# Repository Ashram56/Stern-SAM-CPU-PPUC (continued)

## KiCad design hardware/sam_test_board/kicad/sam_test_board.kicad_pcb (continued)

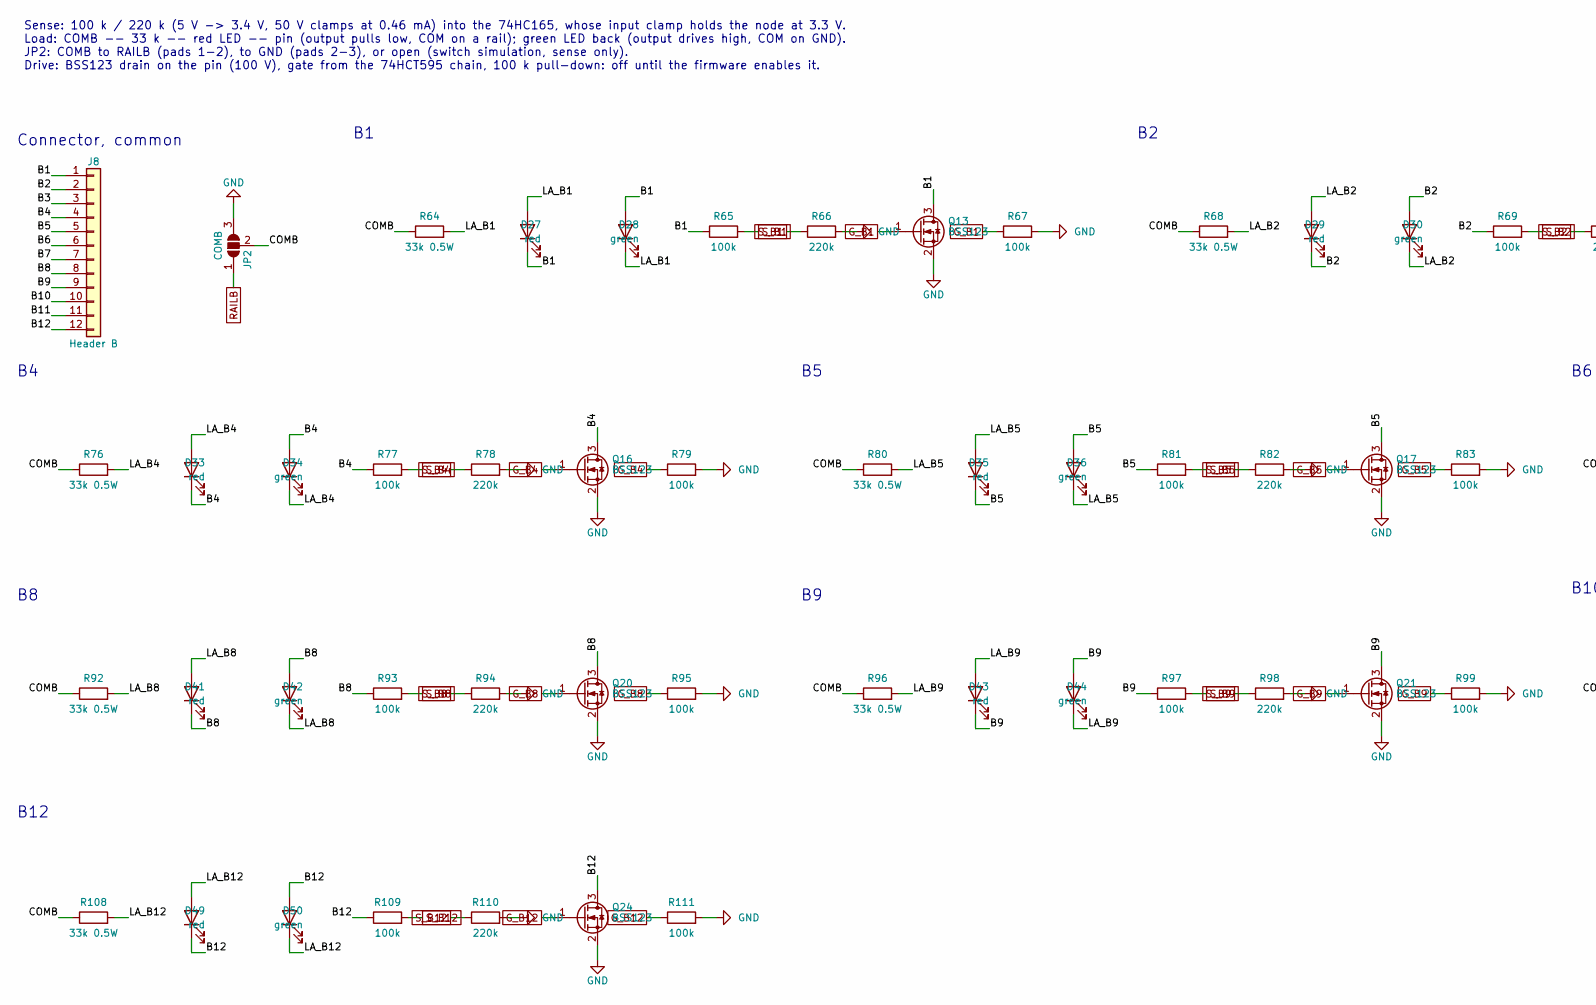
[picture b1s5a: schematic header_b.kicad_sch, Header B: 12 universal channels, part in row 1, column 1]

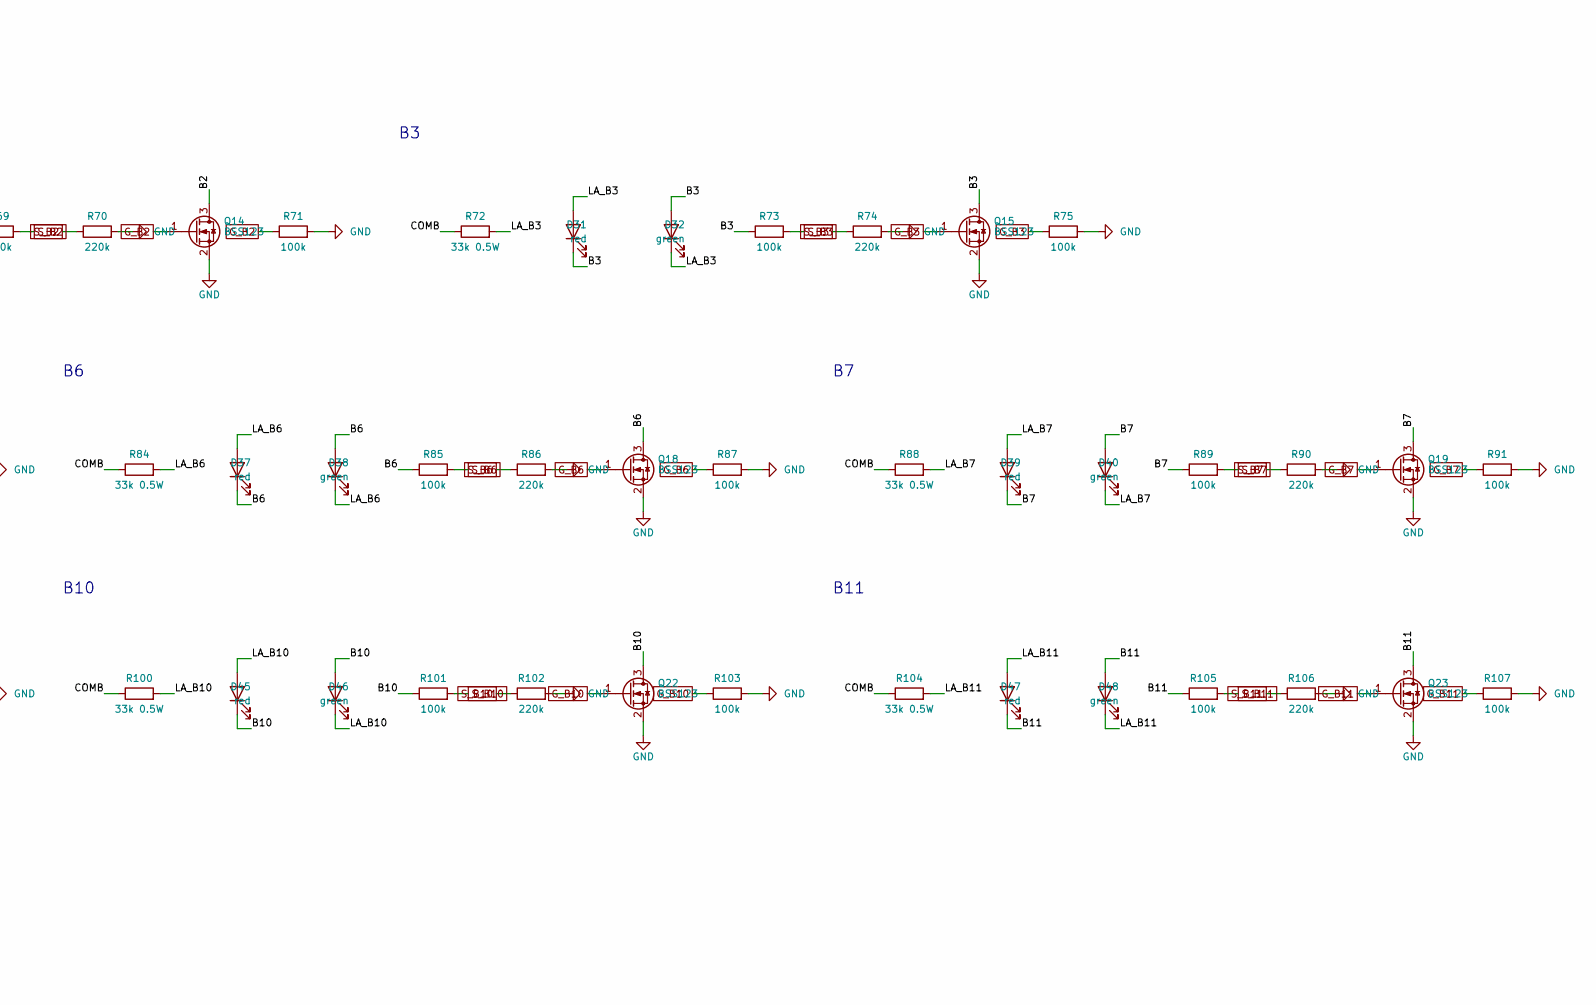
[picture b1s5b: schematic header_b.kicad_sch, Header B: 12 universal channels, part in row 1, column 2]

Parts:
D27, D29, D31, D33, D35, D37, D39, D41, D43, D45, D47, D49: red; LED_0805_2012Metric
D28, D30, D32, D34, D36, D38, D40, D42, D44, D46, D48, D50: green; LED_0805_2012Metric
J8: Header B; Molex_KK-396_A-41791-0012_1x12_P3.96mm_Vertical
JP2: COMB; SolderJumper-3_P1.3mm_Open_Pad1.0x1.5mm
Q13, Q14, Q15, Q16, Q17, Q18, Q19, Q20, Q21, Q22, Q23, Q24: BSS123; SOT-23
R64, R68, R72, R76, R80, R84, R88, R92, R96, R100, R104, R108: 33k 0.5W; R_0805_2012Metric
R65, R67, R69, R71, R73, R75, R77, R79, R81, R83, R85, R87, R89, R91, R93, R95, R97, R99, R101, R103, R105, R107, R109, R111: 100k; R_0805_2012Metric
R66, R70, R74, R78, R82, R86, R90, R94, R98, R102, R106, R110: 220k; R_0805_2012Metric

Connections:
/Header B/B1: D27.1 (K), D28.2 (A), J8.1, Q13.3 (D), R65.1
/Header B/B2: D29.1 (K), D30.2 (A), J8.2, Q14.3 (D), R69.1
/Header B/B3: D31.1 (K), D32.2 (A), J8.3, Q15.3 (D), R73.1
/Header B/B4: D33.1 (K), D34.2 (A), J8.4, Q16.3 (D), R77.1
/Header B/B5: D35.1 (K), D36.2 (A), J8.5, Q17.3 (D), R81.1
/Header B/B6: D37.1 (K), D38.2 (A), J8.6, Q18.3 (D), R85.1
/Header B/B7: D39.1 (K), D40.2 (A), J8.7, Q19.3 (D), R89.1
/Header B/B8: D41.1 (K), D42.2 (A), J8.8, Q20.3 (D), R93.1
/Header B/B9: D43.1 (K), D44.2 (A), J8.9, Q21.3 (D), R97.1
/Header B/B10: D45.1 (K), D46.2 (A), J8.10, Q22.3 (D), R101.1
/Header B/B11: D47.1 (K), D48.2 (A), J8.11, Q23.3 (D), R105.1
/Header B/B12: D49.1 (K), D50.2 (A), J8.12, Q24.3 (D), R109.1
/Header B/COMB: JP2.2 (C), R64.1, R68.1, R72.1, R76.1, R80.1, R84.1, R88.1, R92.1, R96.1, R100.1, R104.1, R108.1
/Header B/LA_B1: D27.2 (A), D28.1 (K), R64.2
/Header B/LA_B2: D29.2 (A), D30.1 (K), R68.2
/Header B/LA_B3: D31.2 (A), D32.1 (K), R72.2
/Header B/LA_B4: D33.2 (A), D34.1 (K), R76.2
/Header B/LA_B5: D35.2 (A), D36.1 (K), R80.2
/Header B/LA_B6: D37.2 (A), D38.1 (K), R84.2
/Header B/LA_B7: D39.2 (A), D40.1 (K), R88.2
/Header B/LA_B8: D41.2 (A), D42.1 (K), R92.2
/Header B/LA_B9: D43.2 (A), D44.1 (K), R96.2
/Header B/LA_B10: D45.2 (A), D46.1 (K), R100.2
/Header B/LA_B11: D47.2 (A), D48.1 (K), R104.2
/Header B/LA_B12: D49.2 (A), D50.1 (K), R108.2
GND: JP2.3 (B), Q13.2 (S), Q14.2 (S), Q15.2 (S), Q16.2 (S), Q17.2 (S), Q18.2 (S), Q19.2 (S), Q20.2 (S), Q21.2 (S), Q22.2 (S), Q23.2 (S), Q24.2 (S), R66.2, R67.2, R70.2, R71.2, R74.2, R75.2, R78.2, R79.2, R82.2, R83.2, R86.2, R87.2, R90.2, R91.2, R94.2, R95.2, R98.2, R99.2, R102.2, R103.2, R106.2, R107.2, R110.2, R111.2; also elsewhere on the board
G_B1: Q13.1 (G), R67.1; also elsewhere on the board
G_B2: Q14.1 (G), R71.1; also elsewhere on the board
G_B3: Q15.1 (G), R75.1; also elsewhere on the board
G_B4: Q16.1 (G), R79.1; also elsewhere on the board
G_B5: Q17.1 (G), R83.1; also elsewhere on the board
G_B6: Q18.1 (G), R87.1; also elsewhere on the board
G_B7: Q19.1 (G), R91.1; also elsewhere on the board
G_B8: Q20.1 (G), R95.1; also elsewhere on the board
G_B9: Q21.1 (G), R99.1; also elsewhere on the board
G_B10: Q22.1 (G), R103.1; also elsewhere on the board
G_B11: Q23.1 (G), R107.1; also elsewhere on the board
G_B12: Q24.1 (G), R111.1; also elsewhere on the board
RAILB: JP2.1 (A); also elsewhere on the board
S_B1: R65.2, R66.1; also elsewhere on the board
S_B2: R69.2, R70.1; also elsewhere on the board
S_B3: R73.2, R74.1; also elsewhere on the board
S_B4: R77.2, R78.1; also elsewhere on the board
S_B5: R81.2, R82.1; also elsewhere on the board
S_B6: R85.2, R86.1; also elsewhere on the board
S_B7: R89.2, R90.1; also elsewhere on the board
S_B8: R93.2, R94.1; also elsewhere on the board
S_B9: R97.2, R98.1; also elsewhere on the board
S_B10: R101.2, R102.1; also elsewhere on the board
S_B11: R105.2, R106.1; also elsewhere on the board
S_B12: R109.2, R110.1; also elsewhere on the board

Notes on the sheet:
Sense: 100 k / 220 k (5 V -> 3.4 V, 50 V clamps at 0.46 mA) into the 74HC165, whose input clamp holds the node at 3.3 V. Load: COMB -- 33 k -- red LED -- pin (output pulls low, COM on a rail); green LED back (output drives high, COM on GND). JP2: COMB to RAILB (pads 1-2), to GND (pads 2-3), or open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
Connector, common
B10
B11
B12

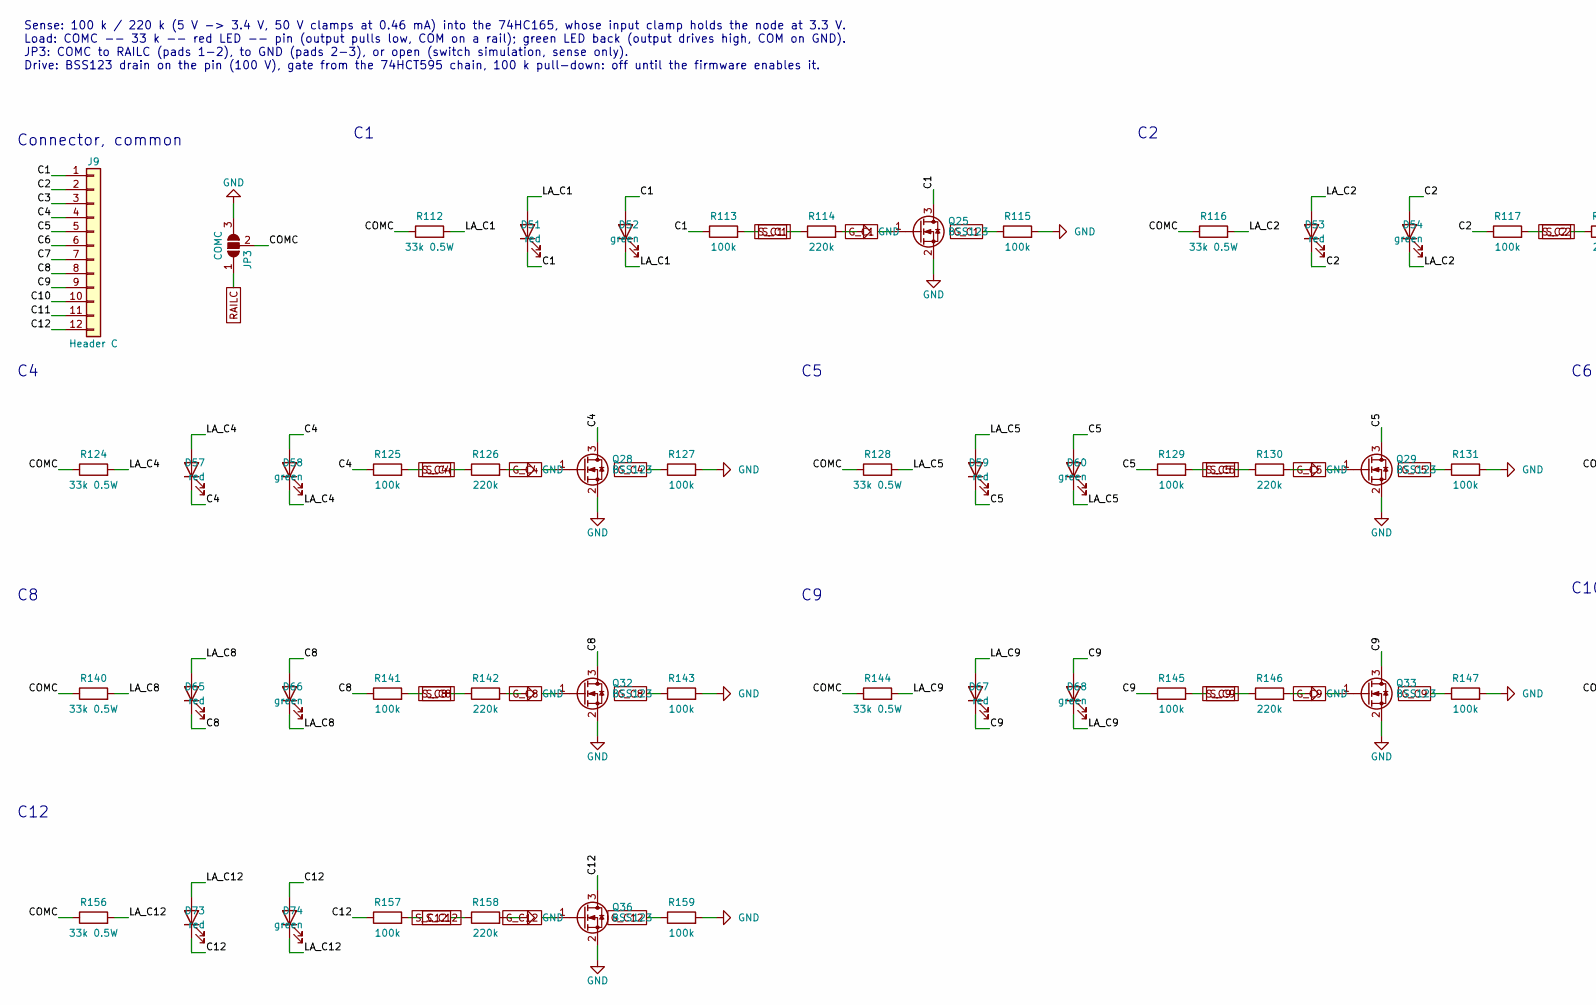
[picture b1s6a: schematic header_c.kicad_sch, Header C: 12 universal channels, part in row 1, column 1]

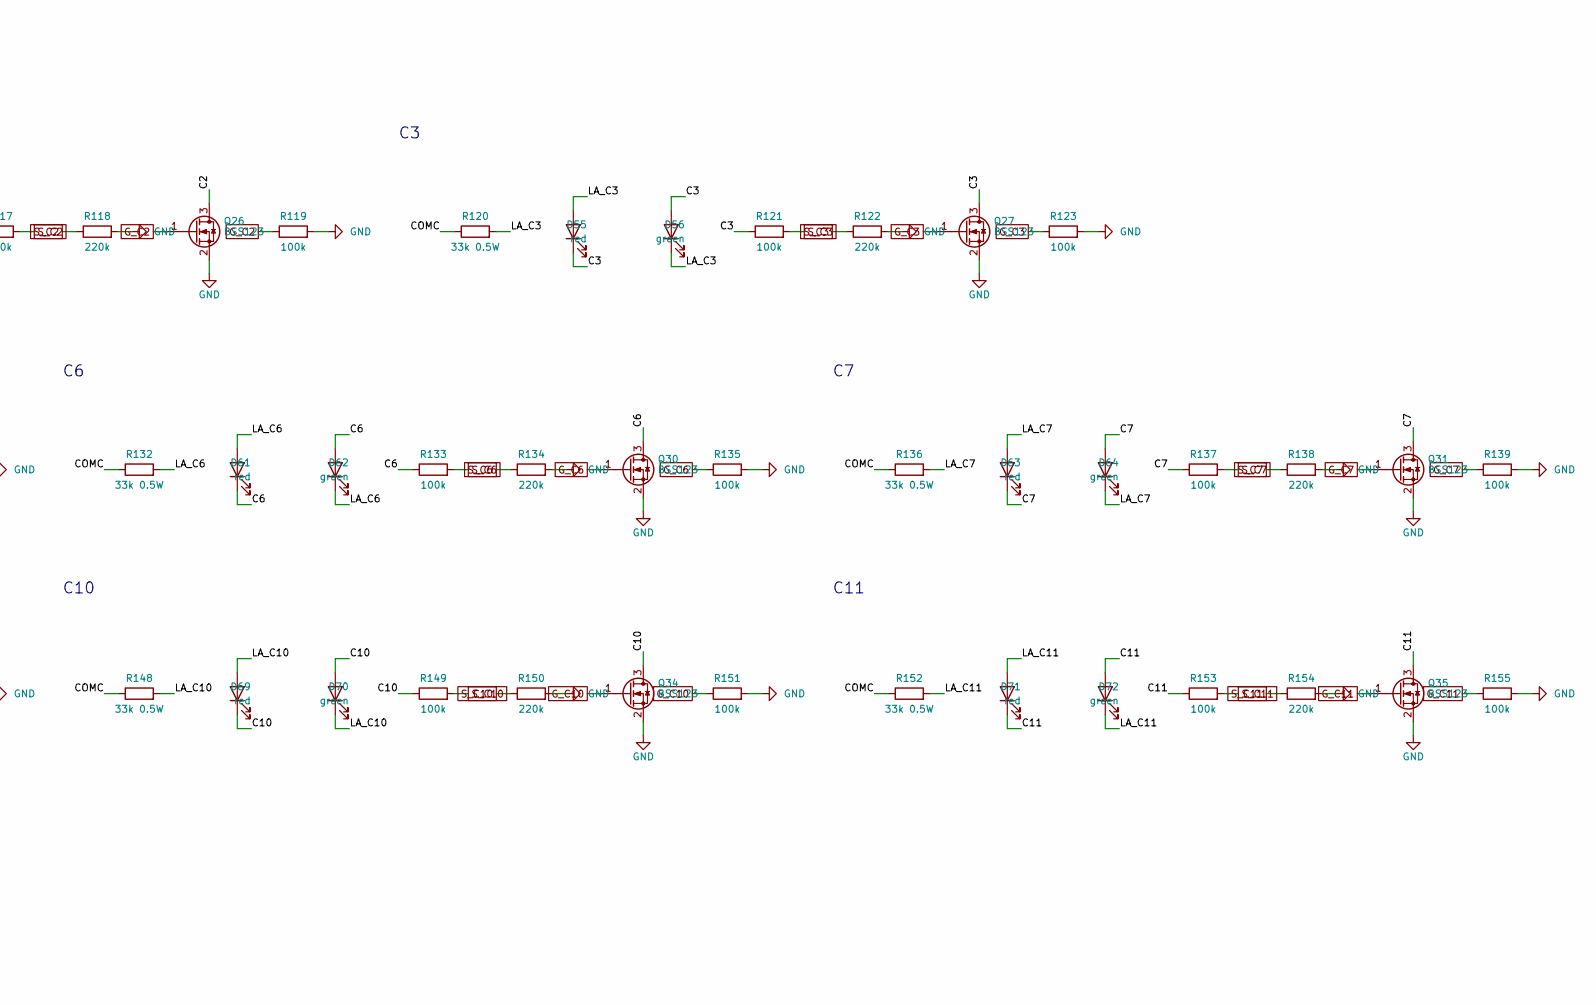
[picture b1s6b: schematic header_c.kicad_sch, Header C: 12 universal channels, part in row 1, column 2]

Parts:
D51, D53, D55, D57, D59, D61, D63, D65, D67, D69, D71, D73: red; LED_0805_2012Metric
D52, D54, D56, D58, D60, D62, D64, D66, D68, D70, D72, D74: green; LED_0805_2012Metric
J9: Header C; Molex_KK-396_A-41791-0012_1x12_P3.96mm_Vertical
JP3: COMC; SolderJumper-3_P1.3mm_Open_Pad1.0x1.5mm
Q25, Q26, Q27, Q28, Q29, Q30, Q31, Q32, Q33, Q34, Q35, Q36: BSS123; SOT-23
R112, R116, R120, R124, R128, R132, R136, R140, R144, R148, R152, R156: 33k 0.5W; R_0805_2012Metric
R113, R115, R117, R119, R121, R123, R125, R127, R129, R131, R133, R135, R137, R139, R141, R143, R145, R147, R149, R151, R153, R155, R157, R159: 100k; R_0805_2012Metric
R114, R118, R122, R126, R130, R134, R138, R142, R146, R150, R154, R158: 220k; R_0805_2012Metric

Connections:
/Header C/C1: D51.1 (K), D52.2 (A), J9.1, Q25.3 (D), R113.1
/Header C/C2: D53.1 (K), D54.2 (A), J9.2, Q26.3 (D), R117.1
/Header C/C3: D55.1 (K), D56.2 (A), J9.3, Q27.3 (D), R121.1
/Header C/C4: D57.1 (K), D58.2 (A), J9.4, Q28.3 (D), R125.1
/Header C/C5: D59.1 (K), D60.2 (A), J9.5, Q29.3 (D), R129.1
/Header C/C6: D61.1 (K), D62.2 (A), J9.6, Q30.3 (D), R133.1
/Header C/C7: D63.1 (K), D64.2 (A), J9.7, Q31.3 (D), R137.1
/Header C/C8: D65.1 (K), D66.2 (A), J9.8, Q32.3 (D), R141.1
/Header C/C9: D67.1 (K), D68.2 (A), J9.9, Q33.3 (D), R145.1
/Header C/C10: D69.1 (K), D70.2 (A), J9.10, Q34.3 (D), R149.1
/Header C/C11: D71.1 (K), D72.2 (A), J9.11, Q35.3 (D), R153.1
/Header C/C12: D73.1 (K), D74.2 (A), J9.12, Q36.3 (D), R157.1
/Header C/COMC: JP3.2 (C), R112.1, R116.1, R120.1, R124.1, R128.1, R132.1, R136.1, R140.1, R144.1, R148.1, R152.1, R156.1
/Header C/LA_C1: D51.2 (A), D52.1 (K), R112.2
/Header C/LA_C2: D53.2 (A), D54.1 (K), R116.2
/Header C/LA_C3: D55.2 (A), D56.1 (K), R120.2
/Header C/LA_C4: D57.2 (A), D58.1 (K), R124.2
/Header C/LA_C5: D59.2 (A), D60.1 (K), R128.2
/Header C/LA_C6: D61.2 (A), D62.1 (K), R132.2
/Header C/LA_C7: D63.2 (A), D64.1 (K), R136.2
/Header C/LA_C8: D65.2 (A), D66.1 (K), R140.2
/Header C/LA_C9: D67.2 (A), D68.1 (K), R144.2
/Header C/LA_C10: D69.2 (A), D70.1 (K), R148.2
/Header C/LA_C11: D71.2 (A), D72.1 (K), R152.2
/Header C/LA_C12: D73.2 (A), D74.1 (K), R156.2
GND: JP3.3 (B), Q25.2 (S), Q26.2 (S), Q27.2 (S), Q28.2 (S), Q29.2 (S), Q30.2 (S), Q31.2 (S), Q32.2 (S), Q33.2 (S), Q34.2 (S), Q35.2 (S), Q36.2 (S), R114.2, R115.2, R118.2, R119.2, R122.2, R123.2, R126.2, R127.2, R130.2, R131.2, R134.2, R135.2, R138.2, R139.2, R142.2, R143.2, R146.2, R147.2, R150.2, R151.2, R154.2, R155.2, R158.2, R159.2; also elsewhere on the board
G_C1: Q25.1 (G), R115.1; also elsewhere on the board
G_C2: Q26.1 (G), R119.1; also elsewhere on the board
G_C3: Q27.1 (G), R123.1; also elsewhere on the board
G_C4: Q28.1 (G), R127.1; also elsewhere on the board
G_C5: Q29.1 (G), R131.1; also elsewhere on the board
G_C6: Q30.1 (G), R135.1; also elsewhere on the board
G_C7: Q31.1 (G), R139.1; also elsewhere on the board
G_C8: Q32.1 (G), R143.1; also elsewhere on the board
G_C9: Q33.1 (G), R147.1; also elsewhere on the board
G_C10: Q34.1 (G), R151.1; also elsewhere on the board
G_C11: Q35.1 (G), R155.1; also elsewhere on the board
G_C12: Q36.1 (G), R159.1; also elsewhere on the board
RAILC: JP3.1 (A); also elsewhere on the board
S_C1: R113.2, R114.1; also elsewhere on the board
S_C2: R117.2, R118.1; also elsewhere on the board
S_C3: R121.2, R122.1; also elsewhere on the board
S_C4: R125.2, R126.1; also elsewhere on the board
S_C5: R129.2, R130.1; also elsewhere on the board
S_C6: R133.2, R134.1; also elsewhere on the board
S_C7: R137.2, R138.1; also elsewhere on the board
S_C8: R141.2, R142.1; also elsewhere on the board
S_C9: R145.2, R146.1; also elsewhere on the board
S_C10: R149.2, R150.1; also elsewhere on the board
S_C11: R153.2, R154.1; also elsewhere on the board
S_C12: R157.2, R158.1; also elsewhere on the board

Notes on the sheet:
Sense: 100 k / 220 k (5 V -> 3.4 V, 50 V clamps at 0.46 mA) into the 74HC165, whose input clamp holds the node at 3.3 V. Load: COMC -- 33 k -- red LED -- pin (output pulls low, COM on a rail); green LED back (output drives high, COM on GND). JP3: COMC to RAILC (pads 1-2), to GND (pads 2-3), or open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
Connector, common
C10
C11
C12

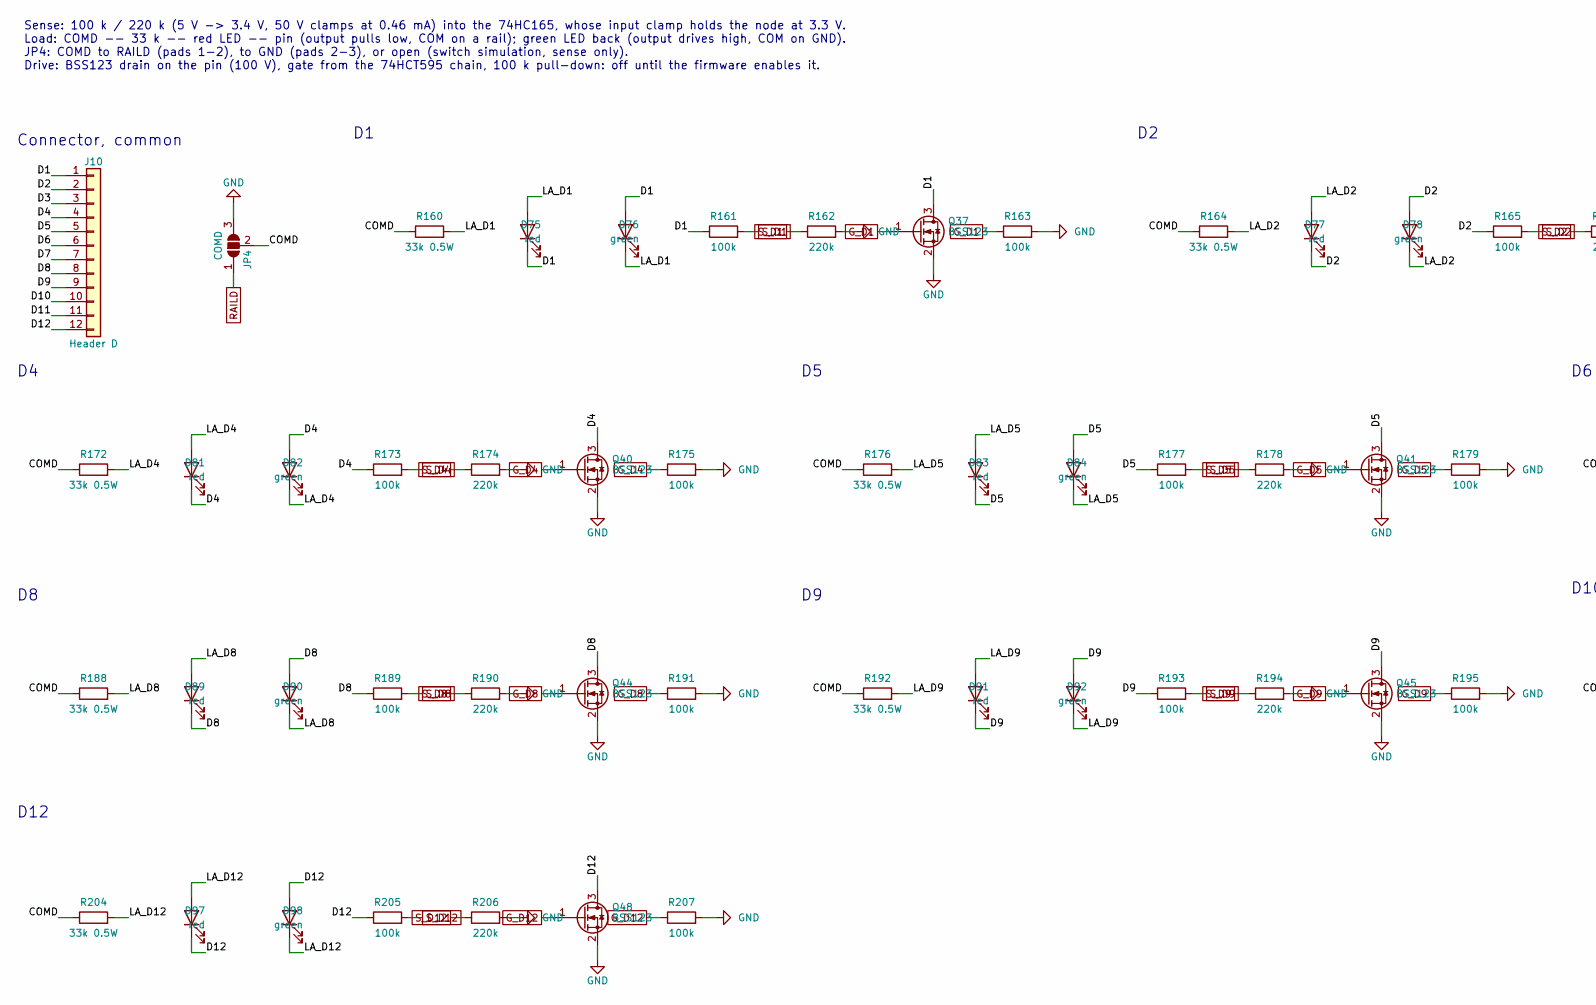
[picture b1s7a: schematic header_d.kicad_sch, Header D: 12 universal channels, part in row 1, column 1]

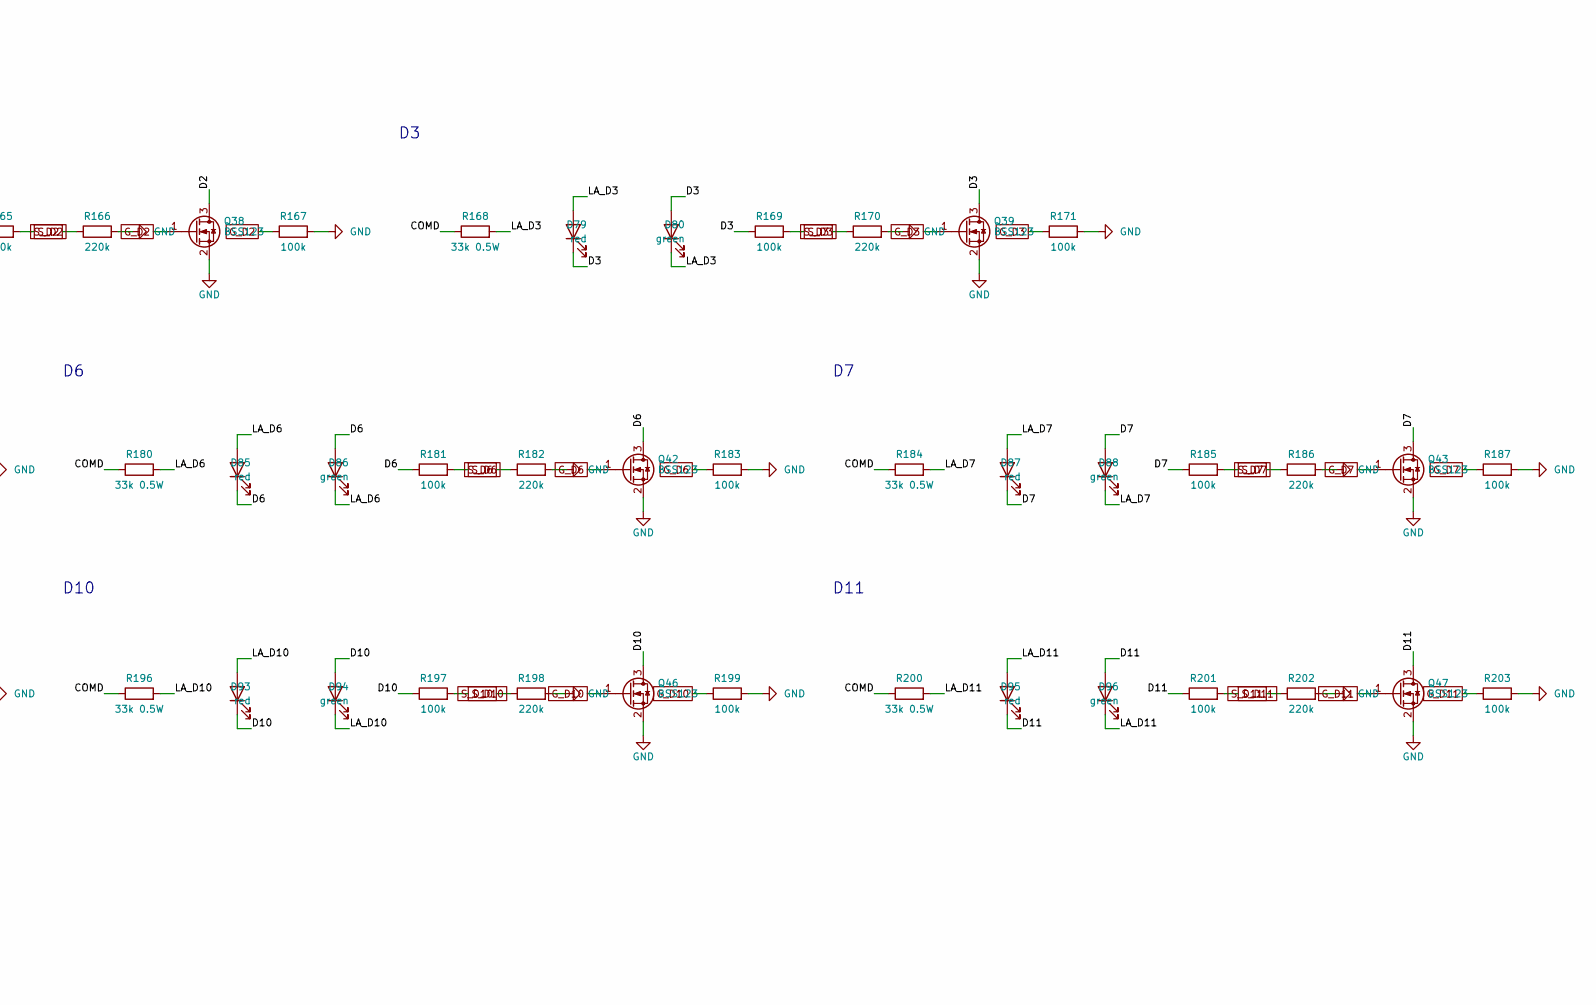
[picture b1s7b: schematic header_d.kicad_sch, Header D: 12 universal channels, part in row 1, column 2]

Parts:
D75, D77, D79, D81, D83, D85, D87, D89, D91, D93, D95, D97: red; LED_0805_2012Metric
D76, D78, D80, D82, D84, D86, D88, D90, D92, D94, D96, D98: green; LED_0805_2012Metric
J10: Header D; Molex_KK-396_A-41791-0012_1x12_P3.96mm_Vertical
JP4: COMD; SolderJumper-3_P1.3mm_Open_Pad1.0x1.5mm
Q37, Q38, Q39, Q40, Q41, Q42, Q43, Q44, Q45, Q46, Q47, Q48: BSS123; SOT-23
R160, R164, R168, R172, R176, R180, R184, R188, R192, R196, R200, R204: 33k 0.5W; R_0805_2012Metric
R161, R163, R165, R167, R169, R171, R173, R175, R177, R179, R181, R183, R185, R187, R189, R191, R193, R195, R197, R199, R201, R203, R205, R207: 100k; R_0805_2012Metric
R162, R166, R170, R174, R178, R182, R186, R190, R194, R198, R202, R206: 220k; R_0805_2012Metric

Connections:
/Header D/COMD: JP4.2 (C), R160.1, R164.1, R168.1, R172.1, R176.1, R180.1, R184.1, R188.1, R192.1, R196.1, R200.1, R204.1
/Header D/D1: D75.1 (K), D76.2 (A), J10.1, Q37.3 (D), R161.1
/Header D/D2: D77.1 (K), D78.2 (A), J10.2, Q38.3 (D), R165.1
/Header D/D3: D79.1 (K), D80.2 (A), J10.3, Q39.3 (D), R169.1
/Header D/D4: D81.1 (K), D82.2 (A), J10.4, Q40.3 (D), R173.1
/Header D/D5: D83.1 (K), D84.2 (A), J10.5, Q41.3 (D), R177.1
/Header D/D6: D85.1 (K), D86.2 (A), J10.6, Q42.3 (D), R181.1
/Header D/D7: D87.1 (K), D88.2 (A), J10.7, Q43.3 (D), R185.1
/Header D/D8: D89.1 (K), D90.2 (A), J10.8, Q44.3 (D), R189.1
/Header D/D9: D91.1 (K), D92.2 (A), J10.9, Q45.3 (D), R193.1
/Header D/D10: D93.1 (K), D94.2 (A), J10.10, Q46.3 (D), R197.1
/Header D/D11: D95.1 (K), D96.2 (A), J10.11, Q47.3 (D), R201.1
/Header D/D12: D97.1 (K), D98.2 (A), J10.12, Q48.3 (D), R205.1
/Header D/LA_D1: D75.2 (A), D76.1 (K), R160.2
/Header D/LA_D2: D77.2 (A), D78.1 (K), R164.2
/Header D/LA_D3: D79.2 (A), D80.1 (K), R168.2
/Header D/LA_D4: D81.2 (A), D82.1 (K), R172.2
/Header D/LA_D5: D83.2 (A), D84.1 (K), R176.2
/Header D/LA_D6: D85.2 (A), D86.1 (K), R180.2
/Header D/LA_D7: D87.2 (A), D88.1 (K), R184.2
/Header D/LA_D8: D89.2 (A), D90.1 (K), R188.2
/Header D/LA_D9: D91.2 (A), D92.1 (K), R192.2
/Header D/LA_D10: D93.2 (A), D94.1 (K), R196.2
/Header D/LA_D11: D95.2 (A), D96.1 (K), R200.2
/Header D/LA_D12: D97.2 (A), D98.1 (K), R204.2
GND: JP4.3 (B), Q37.2 (S), Q38.2 (S), Q39.2 (S), Q40.2 (S), Q41.2 (S), Q42.2 (S), Q43.2 (S), Q44.2 (S), Q45.2 (S), Q46.2 (S), Q47.2 (S), Q48.2 (S), R162.2, R163.2, R166.2, R167.2, R170.2, R171.2, R174.2, R175.2, R178.2, R179.2, R182.2, R183.2, R186.2, R187.2, R190.2, R191.2, R194.2, R195.2, R198.2, R199.2, R202.2, R203.2, R206.2, R207.2; also elsewhere on the board
G_D1: Q37.1 (G), R163.1; also elsewhere on the board
G_D2: Q38.1 (G), R167.1; also elsewhere on the board
G_D3: Q39.1 (G), R171.1; also elsewhere on the board
G_D4: Q40.1 (G), R175.1; also elsewhere on the board
G_D5: Q41.1 (G), R179.1; also elsewhere on the board
G_D6: Q42.1 (G), R183.1; also elsewhere on the board
G_D7: Q43.1 (G), R187.1; also elsewhere on the board
G_D8: Q44.1 (G), R191.1; also elsewhere on the board
G_D9: Q45.1 (G), R195.1; also elsewhere on the board
G_D10: Q46.1 (G), R199.1; also elsewhere on the board
G_D11: Q47.1 (G), R203.1; also elsewhere on the board
G_D12: Q48.1 (G), R207.1; also elsewhere on the board
RAILD: JP4.1 (A); also elsewhere on the board
S_D1: R161.2, R162.1; also elsewhere on the board
S_D2: R165.2, R166.1; also elsewhere on the board
S_D3: R169.2, R170.1; also elsewhere on the board
S_D4: R173.2, R174.1; also elsewhere on the board
S_D5: R177.2, R178.1; also elsewhere on the board
S_D6: R181.2, R182.1; also elsewhere on the board
S_D7: R185.2, R186.1; also elsewhere on the board
S_D8: R189.2, R190.1; also elsewhere on the board
S_D9: R193.2, R194.1; also elsewhere on the board
S_D10: R197.2, R198.1; also elsewhere on the board
S_D11: R201.2, R202.1; also elsewhere on the board
S_D12: R205.2, R206.1; also elsewhere on the board

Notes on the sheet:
Sense: 100 k / 220 k (5 V -> 3.4 V, 50 V clamps at 0.46 mA) into the 74HC165, whose input clamp holds the node at 3.3 V. Load: COMD -- 33 k -- red LED -- pin (output pulls low, COM on a rail); green LED back (output drives high, COM on GND). JP4: COMD to RAILD (pads 1-2), to GND (pads 2-3), or open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
Connector, common
D10
D11
D12
